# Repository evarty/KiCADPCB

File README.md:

This is the PCB design for various projects. Some have associated uC code, but that is seperate. There are seperate repos for some projects under evarty. A number of these have GCode as well.

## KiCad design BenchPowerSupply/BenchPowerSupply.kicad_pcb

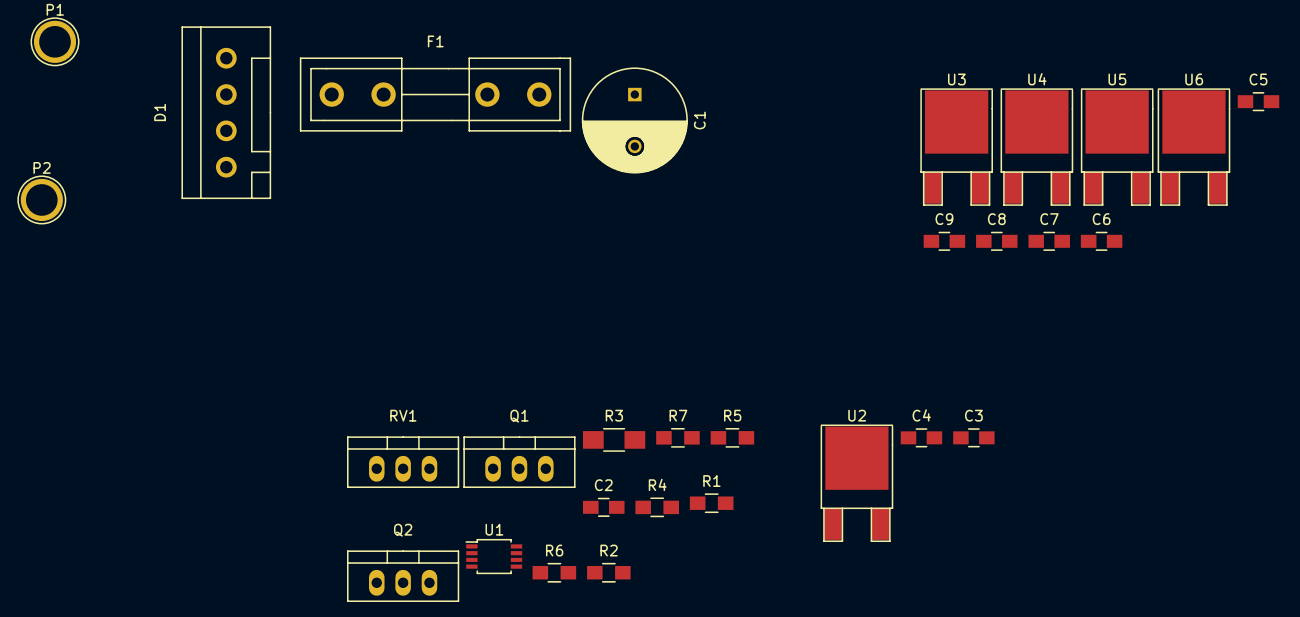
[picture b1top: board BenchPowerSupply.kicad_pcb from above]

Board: 2 copper layers, 29 parts (0 on the bottom side), 17 nets, no tracks yet.

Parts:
C1: 4u7; C_Radial_D10_L13_P5
C2: .1u; C_0805_HandSoldering
C3, C4, C5, C6, C7, C8, C9: C; C_0805_HandSoldering
D1: Diode_Bridge; WAGO_734_4pin_Straight
F1: FUSE; Fuseholder5x20_horiz_open_inline_Type-I
P1, P2: CONN_01X01; 1pin
Q1: Q_NMOS_DGS; TO-220_Neutral123_Vertical
Q2: Q_PMOS_DGS; TO-220_Neutral123_Vertical
R1, R2, R4, R5: 10K; R_0805_HandSoldering
R3: 0R1; R_1206_HandSoldering
R6: 470K; R_0805_HandSoldering
R7: 4K7; R_0805_HandSoldering
RV1: 10K; TO-220_Neutral123_Vertical
U1: TL972; TSSOP-8_3x3mm_Pitch0.65mm
U2, U3: LM7812; TO-252-2Lead
U4: LM7809CT; TO-252-2Lead
U5: LM7805; TO-252-2Lead
U6: LD33V3; TO-252-2Lead

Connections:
15VAC1: D1.4, P1.1
15VAC2: D1.2, P2.1
+12V: C1.2, C2.1, C2.2, C3.2, C4.1, C4.2, C5.2, C6.2, C7.2, C8.2, C9.2, D1.1, Q1.1, R2.2, R7.2, RV1.3, U1.8, U4.2, U6.1
AmplifiedVsense: Q1.3, Q2.2, R6.1, R7.1
unnamed: C6.1, U4.1
unnamed: C7.1, U4.3
unnamed: C8.1, U6.3
unnamed: C9.1, U6.2
unnamed: D1.3, F1.1
unnamed: Q1.2, U1.7
unnamed: R1.2, R2.1, U1.3
unnamed: R4.2, R5.2, U1.2
unnamed: R6.2, RV1.1, RV1.2, U1.6
OutputAfterPassFET: C5.1, Q2.1
OutputAfterRsense: Q2.3, R3.1, R4.1
Rectified: C1.1, C3.1, F1.2, R1.1, R3.2
Vsense: R5.1, U1.1, U1.5

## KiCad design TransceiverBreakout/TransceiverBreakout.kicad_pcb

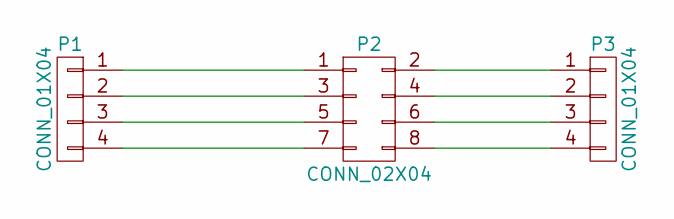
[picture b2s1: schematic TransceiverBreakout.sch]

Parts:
P1, P3: CONN_01X04; Pin_Header_Straight_1x04
P2: CONN_02X04; Pin_Header_Straight_2x04

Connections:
unnamed: P1.1, P2.1
unnamed: P1.2, P2.3
unnamed: P1.3, P2.5
unnamed: P1.4, P2.7
unnamed: P2.2, P3.1
unnamed: P2.4, P3.2
unnamed: P2.6, P3.3
unnamed: P2.8, P3.4

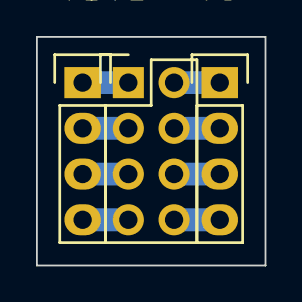
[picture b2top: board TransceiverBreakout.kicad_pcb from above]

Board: 2 copper layers, 12.7 x 12.7 mm, 3 parts (0 on the bottom side), 8 nets.

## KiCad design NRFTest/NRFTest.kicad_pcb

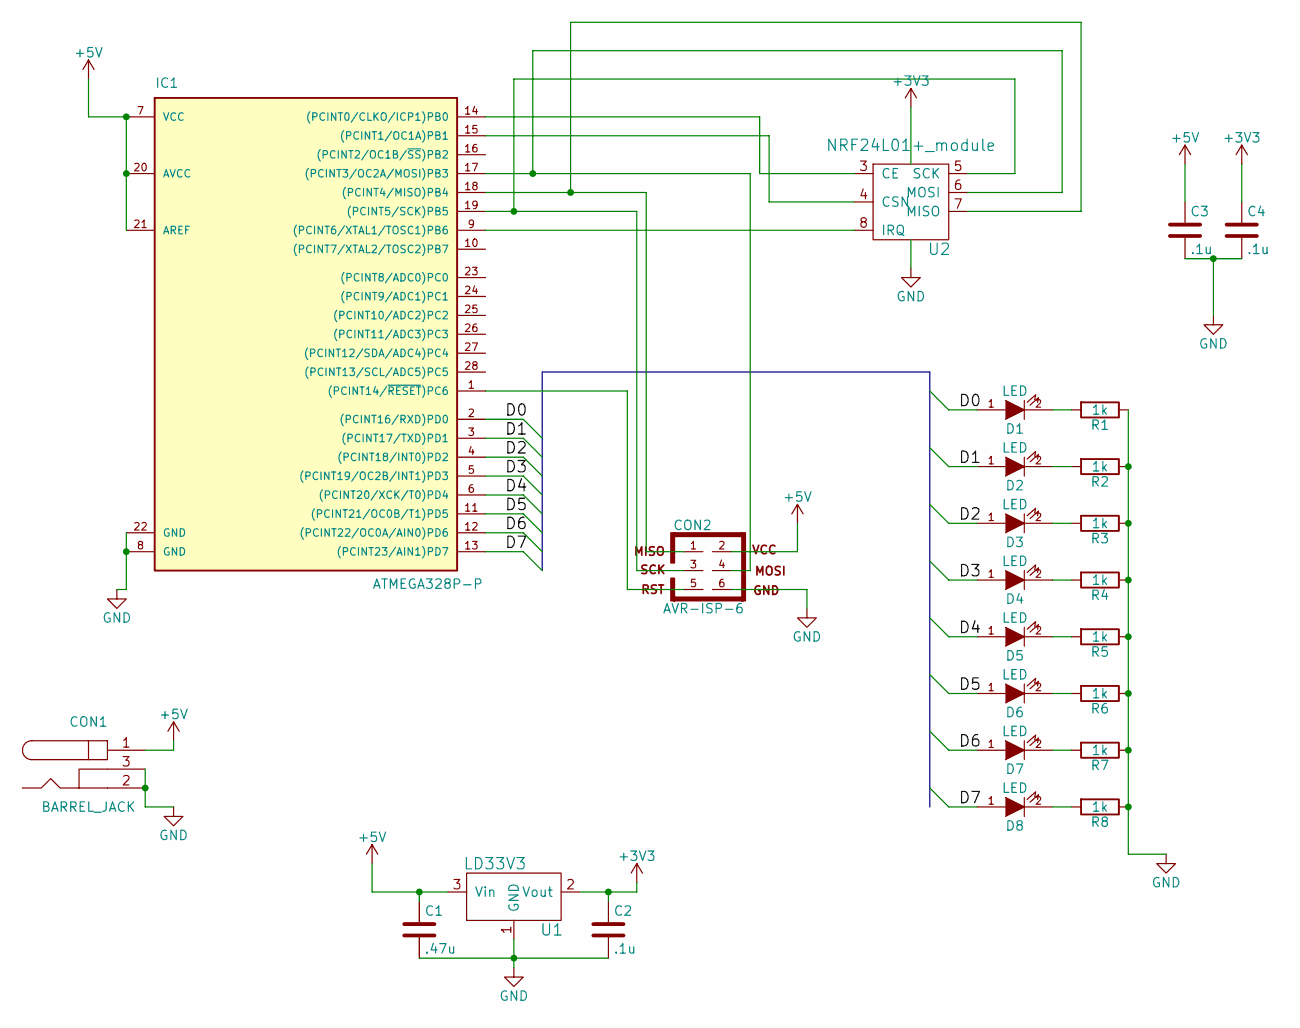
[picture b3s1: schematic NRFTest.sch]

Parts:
C1: .47u; C_Rect_L7_W2.5_P5
C2, C3, C4: .1u; C_Rect_L7_W2.5_P5
CON1: BARREL_JACK
CON2: AVR-ISP-6; Pin_Header_Straight_2x03
D1, D2, D3, D4, D5, D6, D7, D8: LED; LED-5MM
IC1: ATMEGA328P-P; DIP-28_W7.62mm_LongPads
R1, R2, R3, R4, R5, R6, R7, R8: 1k; Resistor_Horizontal_RM15mm
U1: LD33V3; TO-220_Neutral123_Vertical
U2: NRF24L01+_module; Pin_Header_Straight_2x04

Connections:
+3V3: C2.1, C4.1, U1.2 (Vout), U2.1 (GND)
+5V: C1.1, C3.1, CON1.1, CON2.2, IC1.7 (VCC), IC1.20 (AVCC), IC1.21 (AREF), U1.3 (Vin)
/D0: D1.1 (A), IC1.2 ((PCINT16/RXD)PD0)
/D1: D2.1 (A), IC1.3 ((PCINT17/TXD)PD1)
/D2: D3.1 (A), IC1.4 ((PCINT18/INT0)PD2)
/D3: D4.1 (A), IC1.5 ((PCINT19/OC2B/INT1)PD3)
/D4: D5.1 (A), IC1.6 ((PCINT20/XCK/T0)PD4)
/D5: D6.1 (A), IC1.11 ((PCINT21/OC0B/T1)PD5)
/D6: D7.1 (A), IC1.12 ((PCINT22/OC0A/AIN0)PD6)
/D7: D8.1 (A), IC1.13 ((PCINT23/AIN1)PD7)
GND: C1.2, C2.2, C3.2, C4.2, CON1.2, CON1.3, CON2.6, IC1.8 (GND), IC1.22 (GND), R1.1, R2.1, R3.1, R4.1, R5.1, R6.1, R7.1, R8.1, U1.1 (GND), U2.2 (Vcc)
unnamed: CON2.1, IC1.18 ((PCINT4/MISO)PB4), U2.7 (MISO)
unnamed: CON2.3, IC1.19 ((PCINT5/SCK)PB5), U2.5 (SCK)
unnamed: CON2.4, IC1.17 ((PCINT3/OC2A/MOSI)PB3), U2.6 (MOSI)
unnamed: CON2.5, IC1.1 ((PCINT14/~RESET~)PC6)
unnamed: D1.2 (K), R1.2
unnamed: D2.2 (K), R2.2
unnamed: D3.2 (K), R3.2
unnamed: D4.2 (K), R4.2
unnamed: D5.2 (K), R5.2
unnamed: D6.2 (K), R6.2
unnamed: D7.2 (K), R7.2
unnamed: D8.2 (K), R8.2
unnamed: IC1.9 ((PCINT6/XTAL1/TOSC1)PB6), U2.8 (IRQ)
unnamed: IC1.14 ((PCINT0/CLKO/ICP1)PB0), U2.3 (CE)
unnamed: IC1.15 ((PCINT1/OC1A)PB1), U2.4 (CSN)

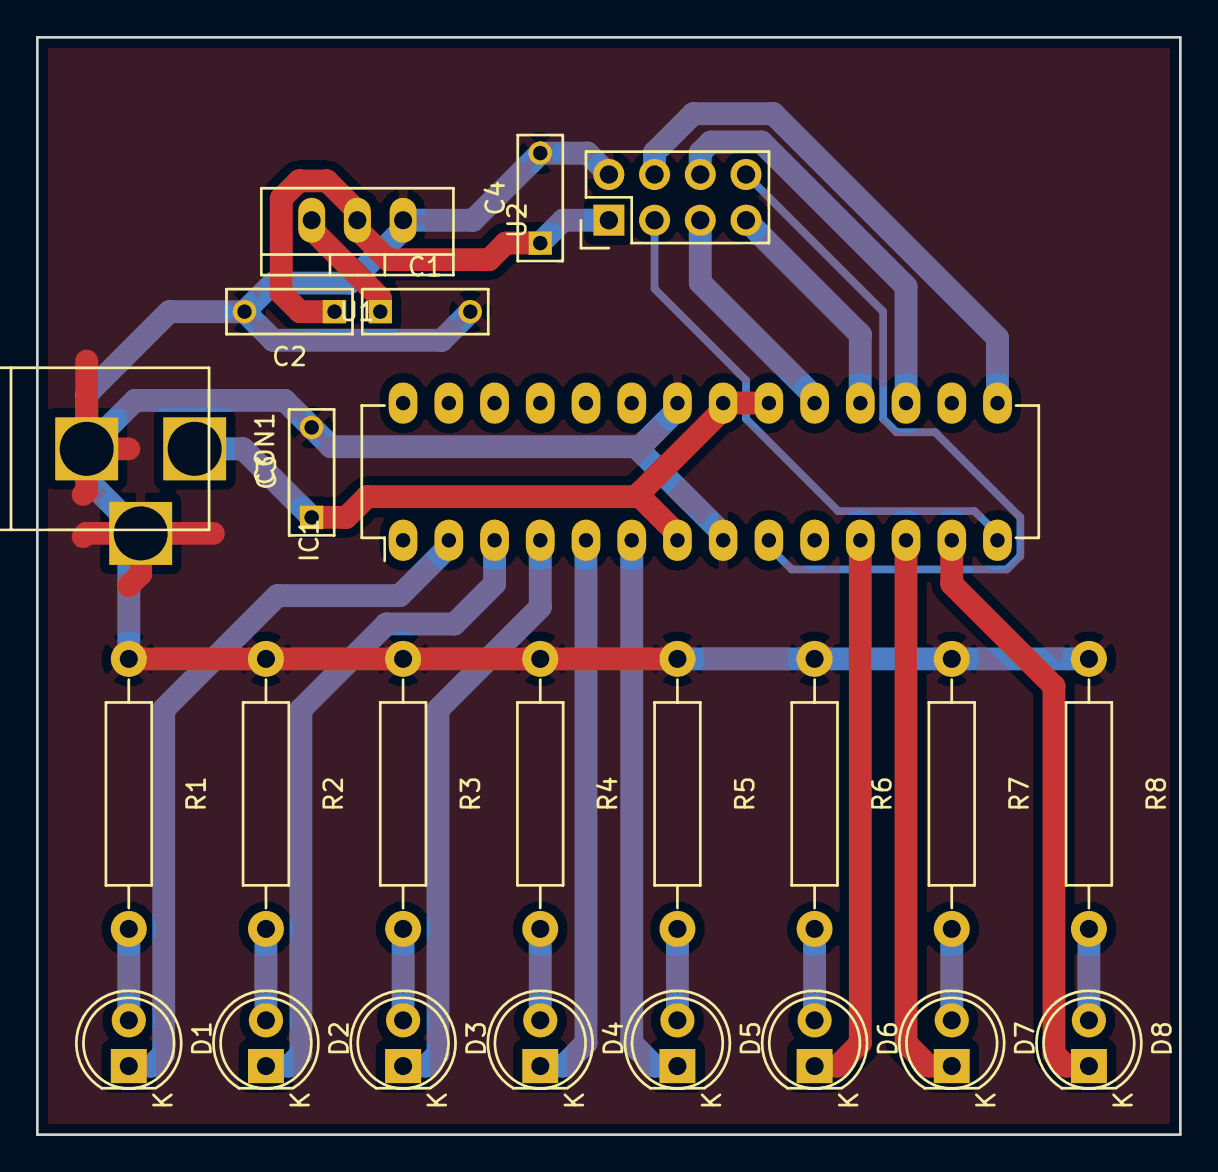
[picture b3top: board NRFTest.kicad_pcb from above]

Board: 2 copper layers, 63.5 x 61.0 mm, 24 parts (0 on the bottom side), 25 nets.

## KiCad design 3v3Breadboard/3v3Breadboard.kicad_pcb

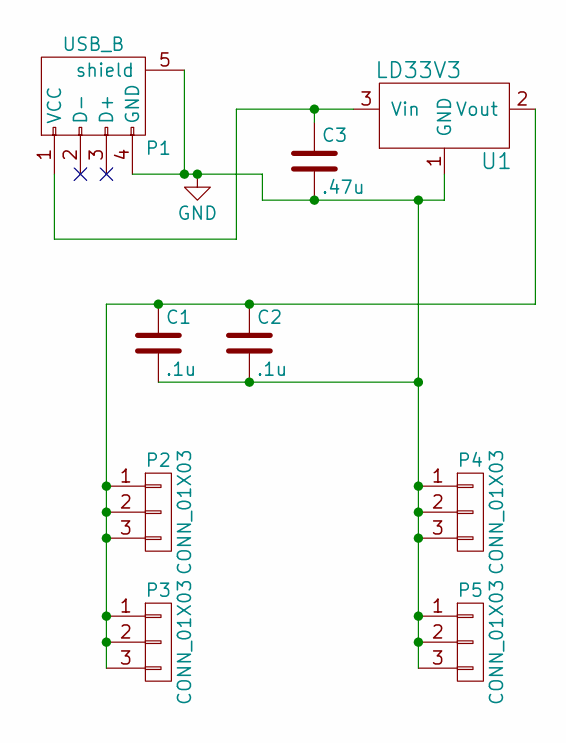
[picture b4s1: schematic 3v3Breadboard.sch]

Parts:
C1, C2: .1u; C_Rect_L7_W2.5_P5
C3: .47u; C_Rect_L7_W2.5_P5
P1: USB_B
P2, P3, P4, P5: CONN_01X03; Pin_Header_Straight_1x03
U1: LD33V3; TO-220_Neutral123_Vertical_LargePads

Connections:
GND: C1.2, C2.2, C3.2, P1.4 (GND), P1.5 (shield), P4.1, P4.2, P4.3, P5.1, P5.2, P5.3, U1.1 (GND)
unnamed: C1.1, C2.1, P2.1, P2.2, P2.3, P3.1, P3.2, P3.3, U1.2 (Vout)
unnamed: C3.1, P1.1 (VCC), U1.3 (Vin)

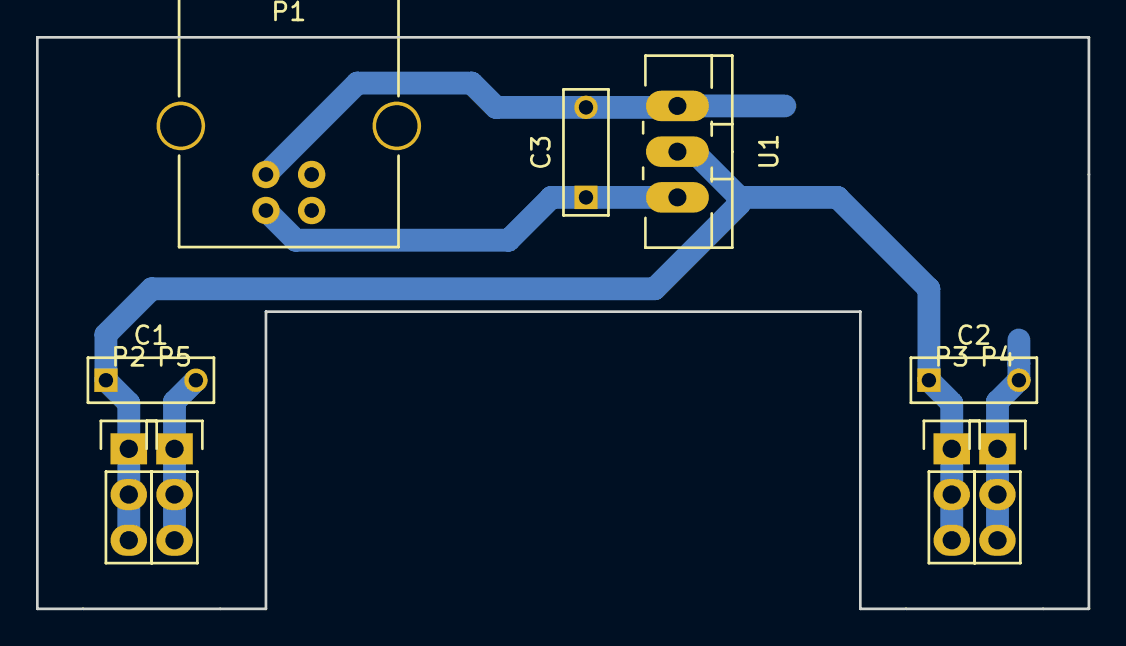
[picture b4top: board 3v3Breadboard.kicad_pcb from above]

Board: 2 copper layers, 58.4 x 31.8 mm, 9 parts (0 on the bottom side), 3 nets.

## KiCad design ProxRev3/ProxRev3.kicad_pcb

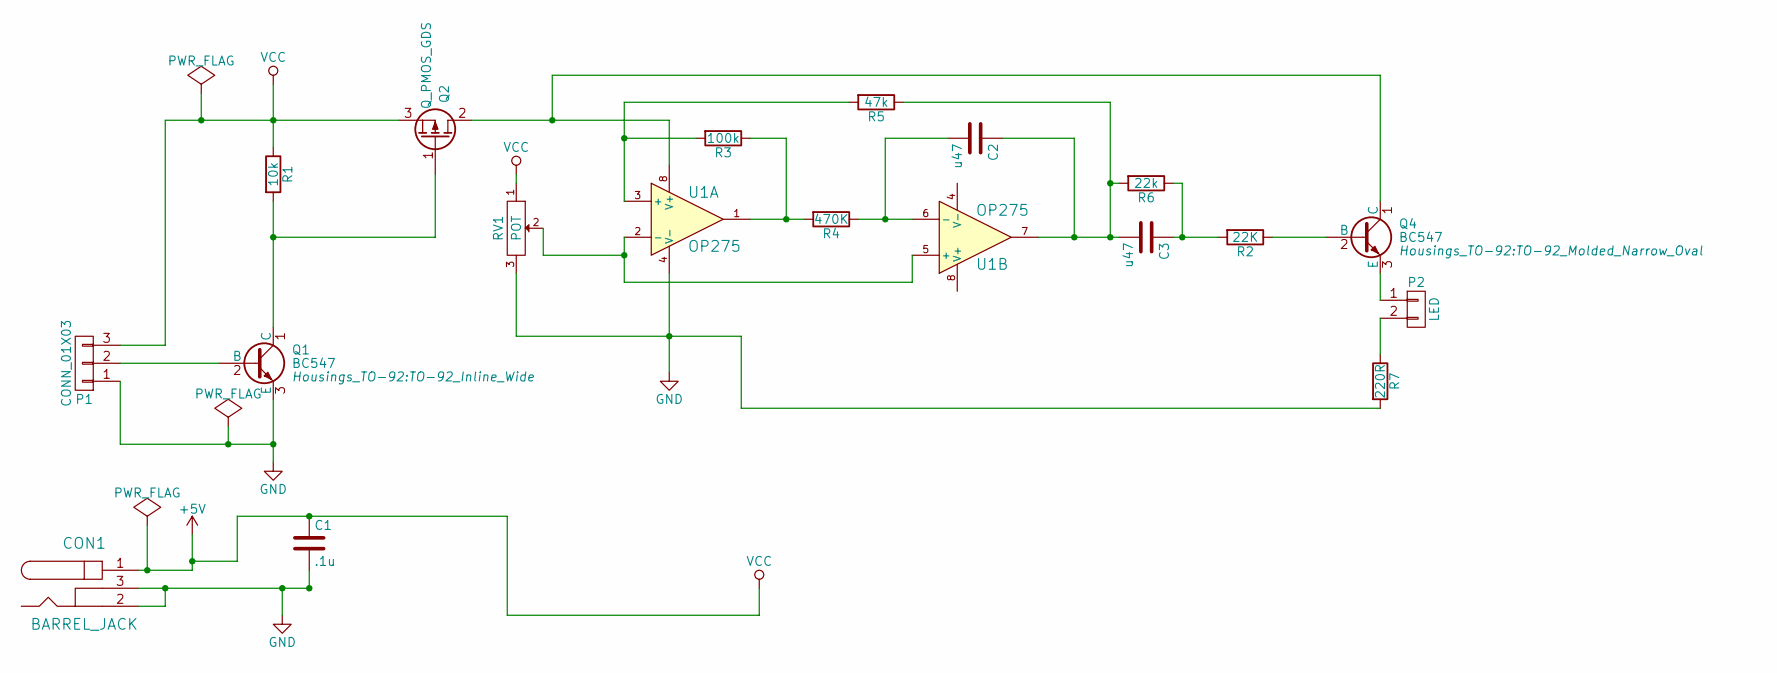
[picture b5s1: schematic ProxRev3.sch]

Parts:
C1: .1u; C_Rect_L7_W2.5_P5
C2, C3: u47; C_Rect_L7_W2.5_P5
CON1: BARREL_JACK
P1: CONN_01X03; Pin_Header_Angled_1x03
P2: LED; Pin_Header_Angled_1x02
Q1: BC547; TO-92_Inline_Wide
Q2: Q_PMOS_GDS; TO-92_Inline_Wide
Q4: BC547; TO-92_Molded_Narrow_Oval
R1: 10k; Resistor_Horizontal_RM10mm
R2: 22K; Resistor_Horizontal_RM10mm
R3: 100k; Resistor_Horizontal_RM10mm
R4: 470K; Resistor_Horizontal_RM10mm
R5: 47k; Resistor_Horizontal_RM10mm
R6: 22k; Resistor_Horizontal_RM10mm
R7: 220R; Resistor_Horizontal_RM10mm
RV1: POT; Potentiometer_Bourns_3339P_Angular_ScrewUp
U1: OP275; DIP-8_W7.62mm_LongPads

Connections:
+5V: C1.1, CON1.1, P1.3, Q2.3 (S), R1.1, RV1.1
GND: C1.2, CON1.2, CON1.3, P1.1, Q1.3 (E), R7.2, RV1.3, U1.4 (V-)
unnamed: C2.1, C3.2, R5.1, R6.2, U1.7
unnamed: C2.2, R4.1, U1.6 (-)
unnamed: C3.1, R2.2, R6.1
unnamed: P1.2, Q1.2 (B)
unnamed: P2.1, Q4.3 (E)
unnamed: P2.2, R7.1
unnamed: Q1.1 (C), Q2.1 (G), R1.2
unnamed: Q2.2 (D), Q4.1 (C), U1.8 (V+)
unnamed: Q4.2 (B), R2.1
unnamed: R3.1, R4.2, U1.1
unnamed: R3.2, R5.2, U1.3 (+)
unnamed: RV1.2, U1.2 (-), U1.5 (+)

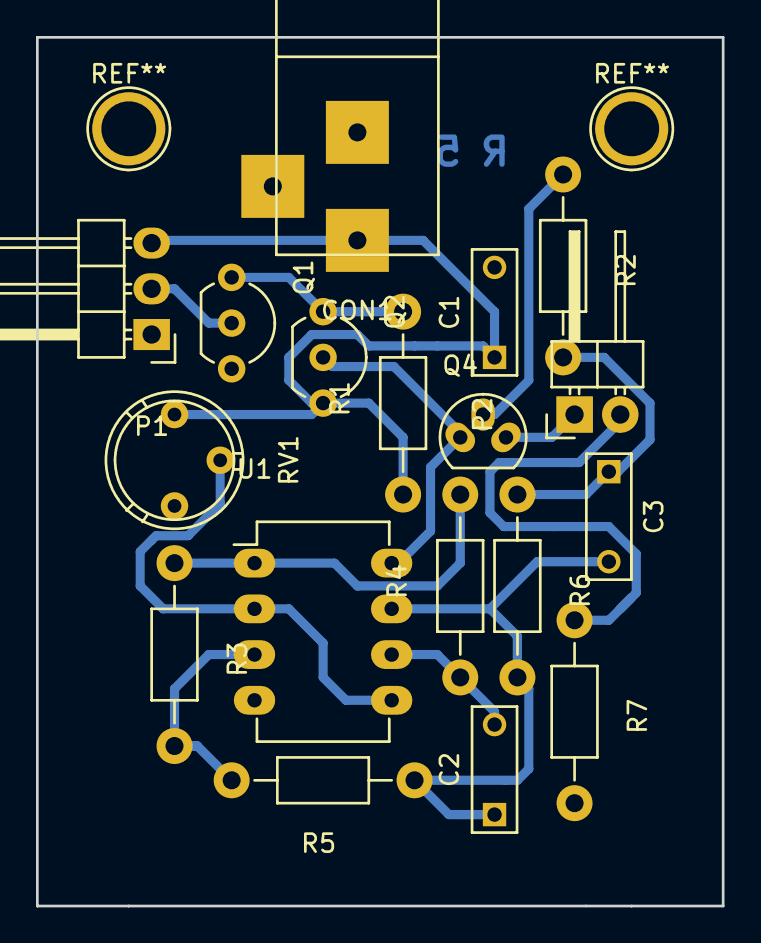
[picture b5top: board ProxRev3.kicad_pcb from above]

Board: 2 copper layers, 38.1 x 48.3 mm, 18 parts (0 on the bottom side), 14 nets.

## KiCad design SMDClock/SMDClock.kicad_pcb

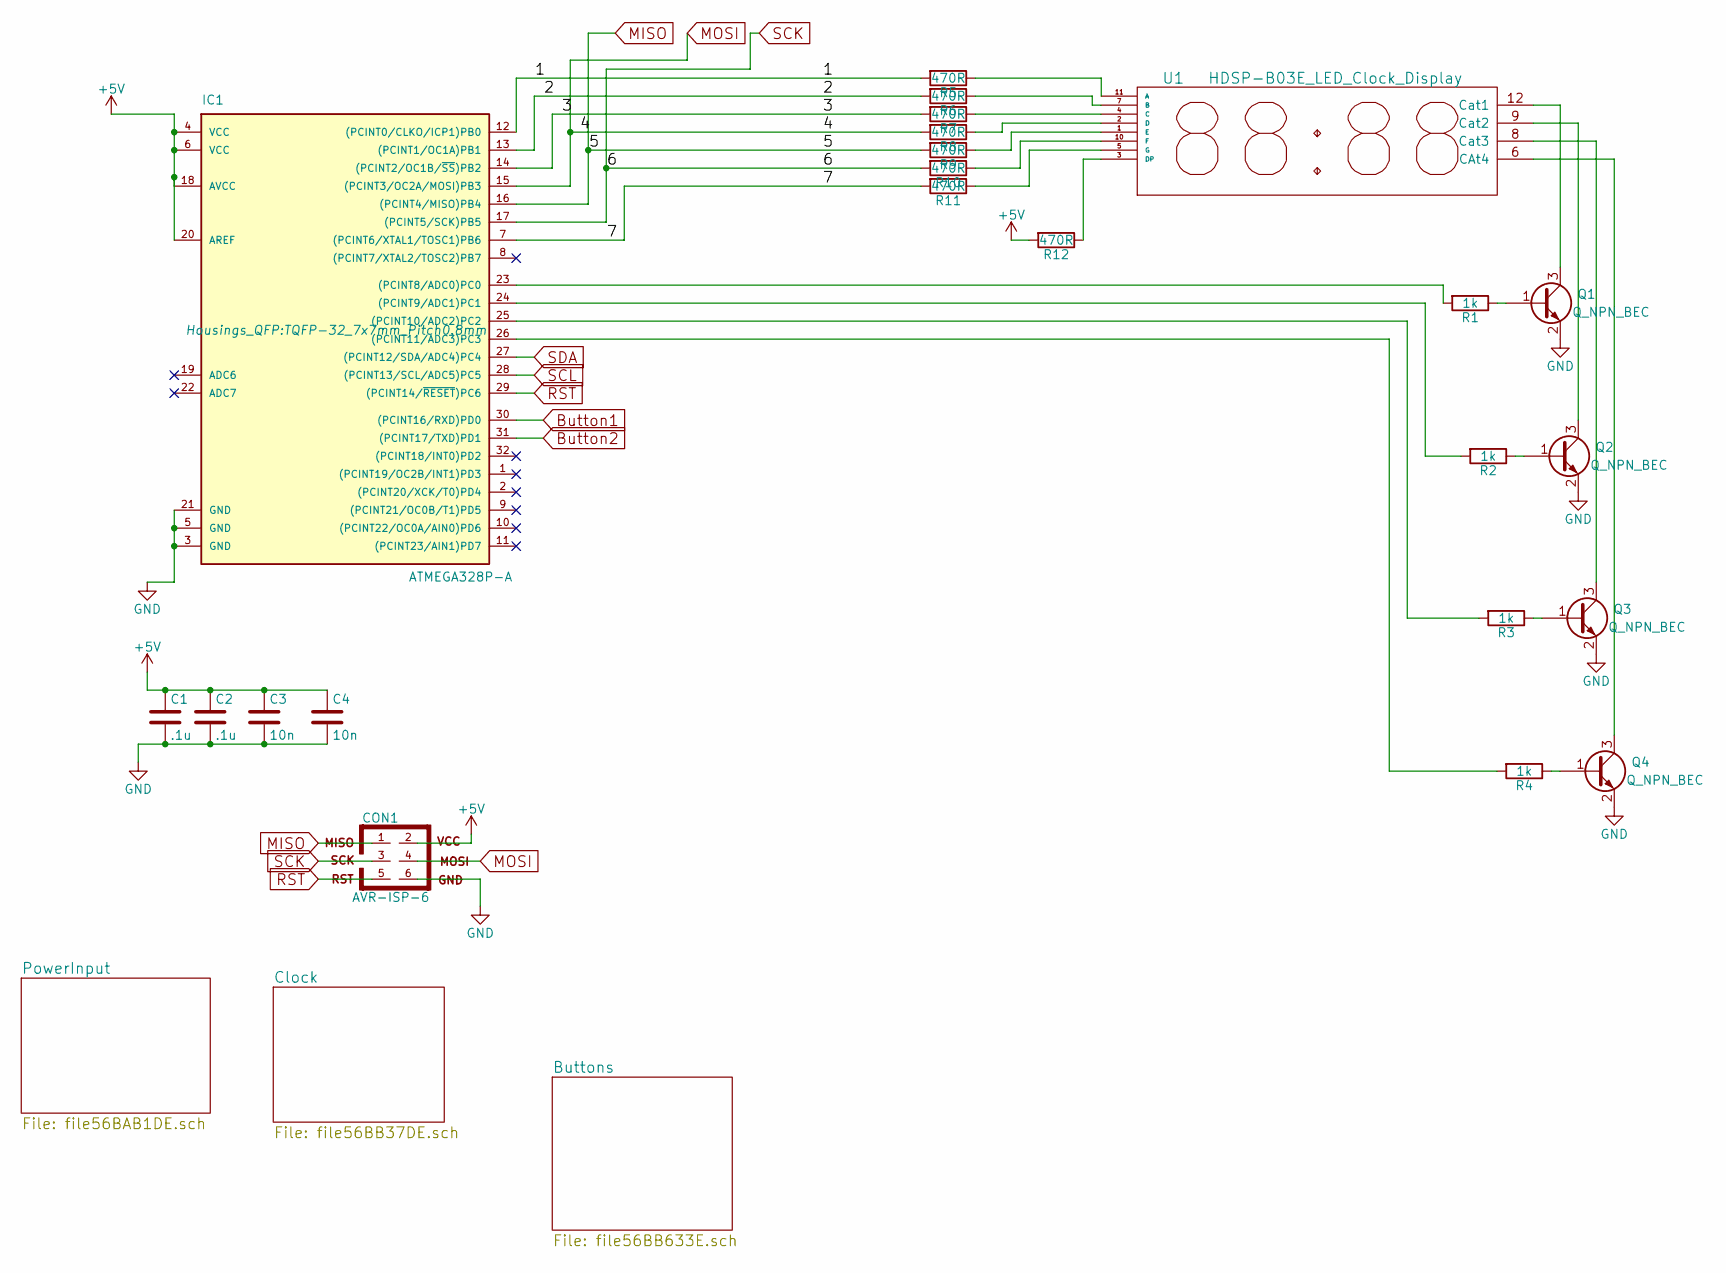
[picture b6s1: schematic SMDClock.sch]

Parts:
C1, C2: .1u; C_0805_HandSoldering
C3, C4: 10n; C_0805_HandSoldering
CON1: AVR-ISP-6; Pin_Header_Straight_2x03
IC1: ATMEGA328P-A; TQFP-32_7x7mm_Pitch0.8mm
Q1, Q2, Q3, Q4: Q_NPN_BEC; SOT-23_Handsoldering
R1, R2, R3, R4: 1k; R_0805_HandSoldering
R5, R6, R7, R8, R9, R10, R11, R12: 470R; R_0805_HandSoldering
U1: HDSP-B03E_LED_Clock_Display; DHDSP-B03E_Footprint

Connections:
+5V: C1.1, C2.1, C3.1, C4.1, CON1.2, IC1.4 (VCC), IC1.6 (VCC), IC1.18 (AVCC), IC1.20 (AREF), R12.2; also elsewhere on the board
/1: IC1.12 ((PCINT0/CLKO/ICP1)PB0), R5.2
/2: IC1.13 ((PCINT1/OC1A)PB1), R6.2
/3: IC1.14 ((PCINT2/OC1B/~SS~)PB2), R7.2
/7: IC1.7 ((PCINT6/XTAL1/TOSC1)PB6), R11.2
Button1: IC1.30 ((PCINT16/RXD)PD0); also elsewhere on the board
Button2: IC1.31 ((PCINT17/TXD)PD1); also elsewhere on the board
GND: C1.2, C2.2, C3.2, C4.2, CON1.6, IC1.3 (GND), IC1.5 (GND), IC1.21 (GND), Q1.2 (E), Q2.2 (E), Q3.2 (E), Q4.2 (E); also elsewhere on the board
MISO: CON1.1, IC1.16 ((PCINT4/MISO)PB4), R9.2
MOSI: CON1.4, IC1.15 ((PCINT3/OC2A/MOSI)PB3), R8.2
unnamed: IC1.23 ((PCINT8/ADC0)PC0), R1.2
unnamed: IC1.24 ((PCINT9/ADC1)PC1), R2.2
unnamed: IC1.25 ((PCINT10/ADC2)PC2), R3.2
unnamed: IC1.26 ((PCINT11/ADC3)PC3), R4.2
unnamed: Q1.1 (B), R1.1
unnamed: Q1.3 (C), U1.12 (Cat1)
unnamed: Q2.1 (B), R2.1
unnamed: Q2.3 (C), U1.9 (Cat2)
unnamed: Q3.1 (B), R3.1
unnamed: Q3.3 (C), U1.8 (Cat3)
unnamed: Q4.1 (B), R4.1
unnamed: Q4.3 (C), U1.6 (CAt4)
unnamed: R5.1, U1.11 (A)
unnamed: R6.1, U1.7 (B)
unnamed: R7.1, U1.4 (C)
unnamed: R8.1, U1.2 (D)
unnamed: R9.1, U1.1 (E)
unnamed: R10.1, U1.10 (F)
unnamed: R11.1, U1.5 (G)
unnamed: R12.1, U1.3 (DP)
RST: CON1.5, IC1.29 ((PCINT14/~RESET~)PC6)
SCK: CON1.3, IC1.17 ((PCINT5/SCK)PB5), R10.2
SCL: IC1.28 ((PCINT13/SCL/ADC5)PC5); also elsewhere on the board
SDA: IC1.27 ((PCINT12/SDA/ADC4)PC4); also elsewhere on the board

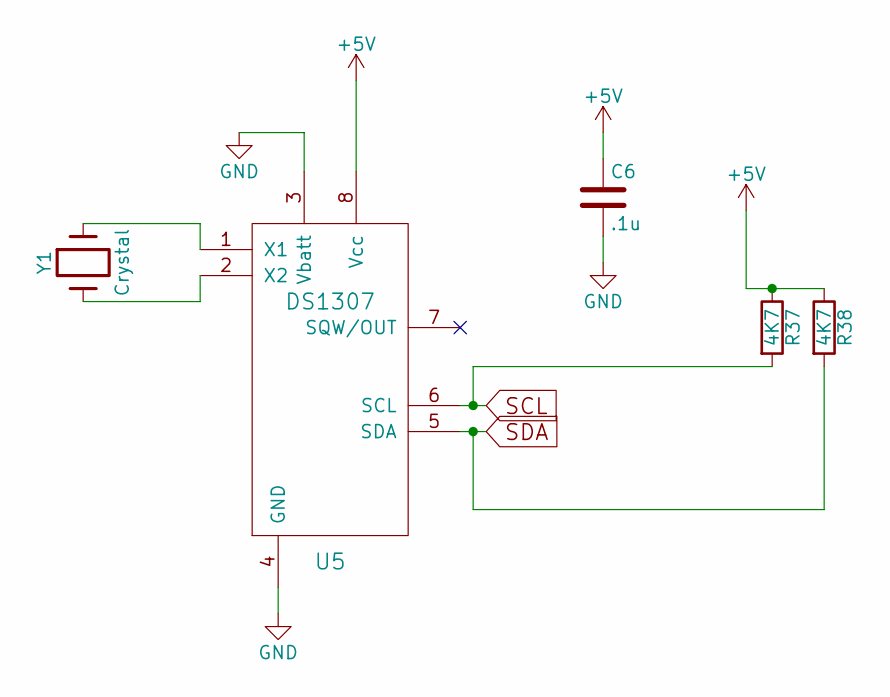
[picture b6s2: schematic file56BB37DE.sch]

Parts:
C6: .1u; C_0805_HandSoldering
R37, R38: 4K7; R_0805_HandSoldering
U5: DS1307; SOIC-8_3.9x4.9mm_Pitch1.27mm
Y1: Crystal; Crystal_Watch

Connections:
+5V: C6.1, R37.1, R38.1, U5.8 (Vcc); also elsewhere on the board
GND: C6.2, U5.3 (Vbatt), U5.4 (GND); also elsewhere on the board
unnamed: U5.1 (X1), Y1.1
unnamed: U5.2 (X2), Y1.2
SCL: R37.2, U5.6 (SCL); also elsewhere on the board
SDA: R38.2, U5.5 (SDA); also elsewhere on the board

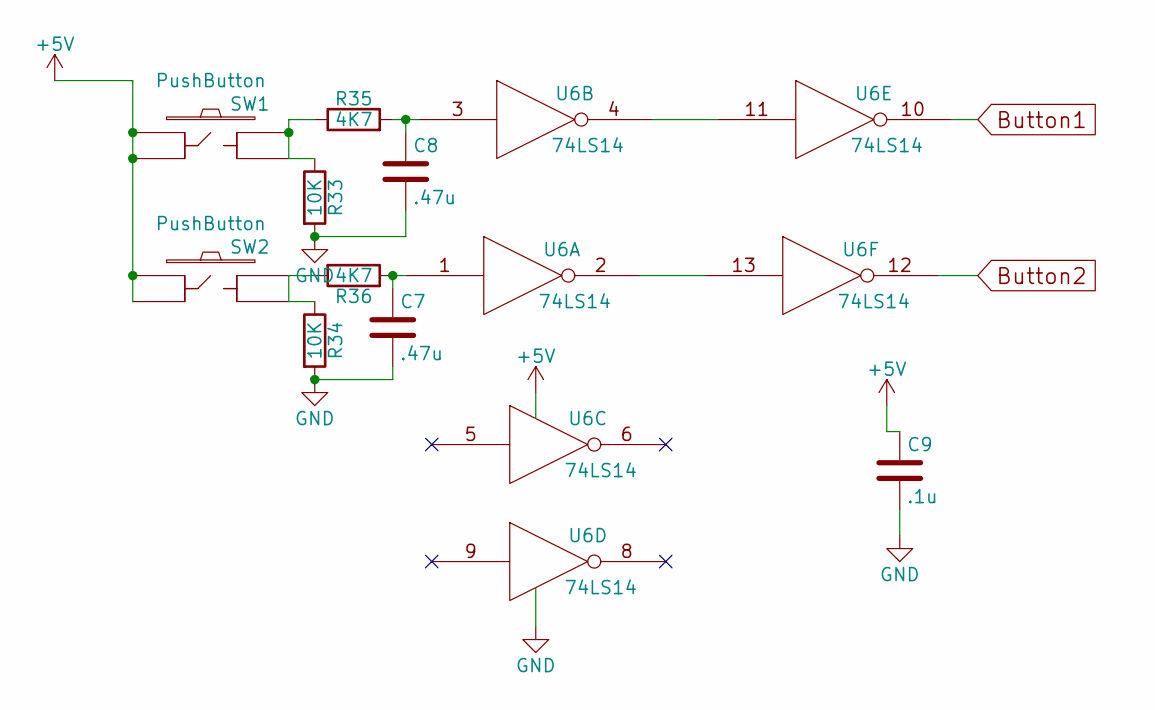
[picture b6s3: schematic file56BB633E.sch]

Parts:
C7, C8: .47u; C_0805_HandSoldering
C9: .1u; C_0805_HandSoldering
R33, R34: 10K; R_0805_HandSoldering
R35, R36: 4K7; R_0805_HandSoldering
SW1, SW2: PushButton
U6: 74LS14; SOIC-14_N

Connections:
+5V: C9.1, SW1.1, SW1.4, SW2.1, SW2.4, U6.14 (VCC); also elsewhere on the board
Button1: U6.10; also elsewhere on the board
Button2: U6.12; also elsewhere on the board
GND: C7.2, C8.2, C9.2, R33.2, R34.2, U6.7 (GND); also elsewhere on the board
unnamed: C7.1, R36.1, U6.1
unnamed: C8.1, R35.2, U6.3
unnamed: R33.1, R35.1, SW1.2, SW1.3
unnamed: R34.1, R36.2, SW2.2, SW2.3
unnamed: U6.4, U6.11
unnamed: U6.2, U6.13

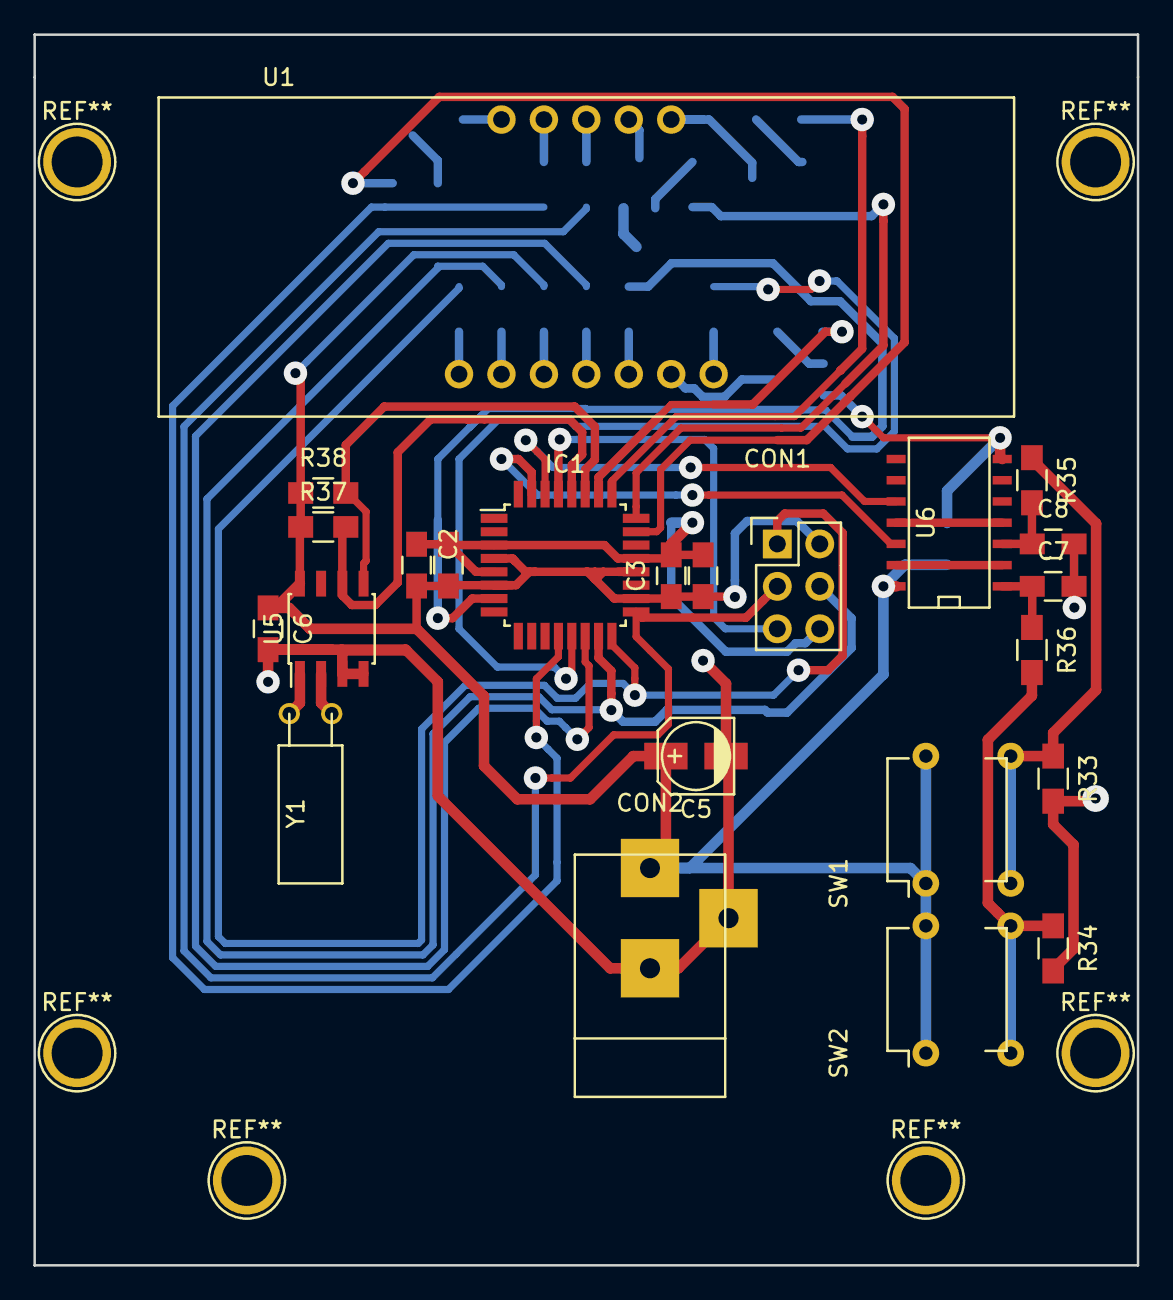
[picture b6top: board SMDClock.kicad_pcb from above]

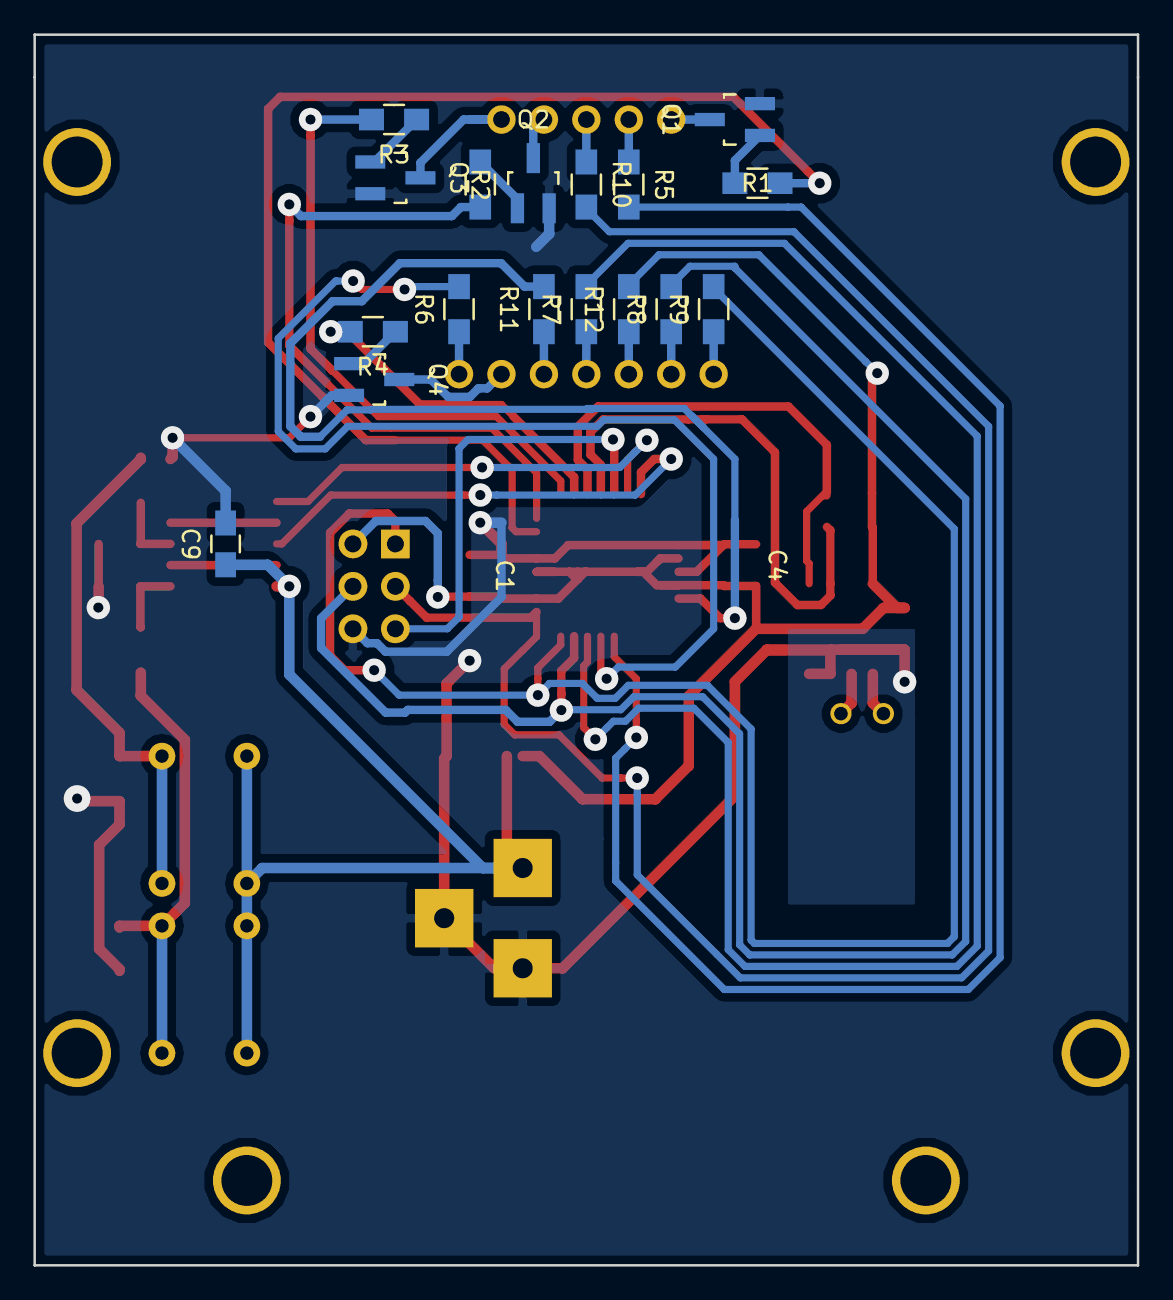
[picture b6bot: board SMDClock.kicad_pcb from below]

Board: 2 copper layers, 66.0 x 73.7 mm, 40 parts (17 on the bottom side), 42 nets.

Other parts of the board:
C5: 100u; c_elec_4x4.5
CON2: BARREL_JACK

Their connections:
+5V: C5.1, CON2.1; also elsewhere on the board
GND: C5.2, CON2.2, CON2.3; also elsewhere on the board

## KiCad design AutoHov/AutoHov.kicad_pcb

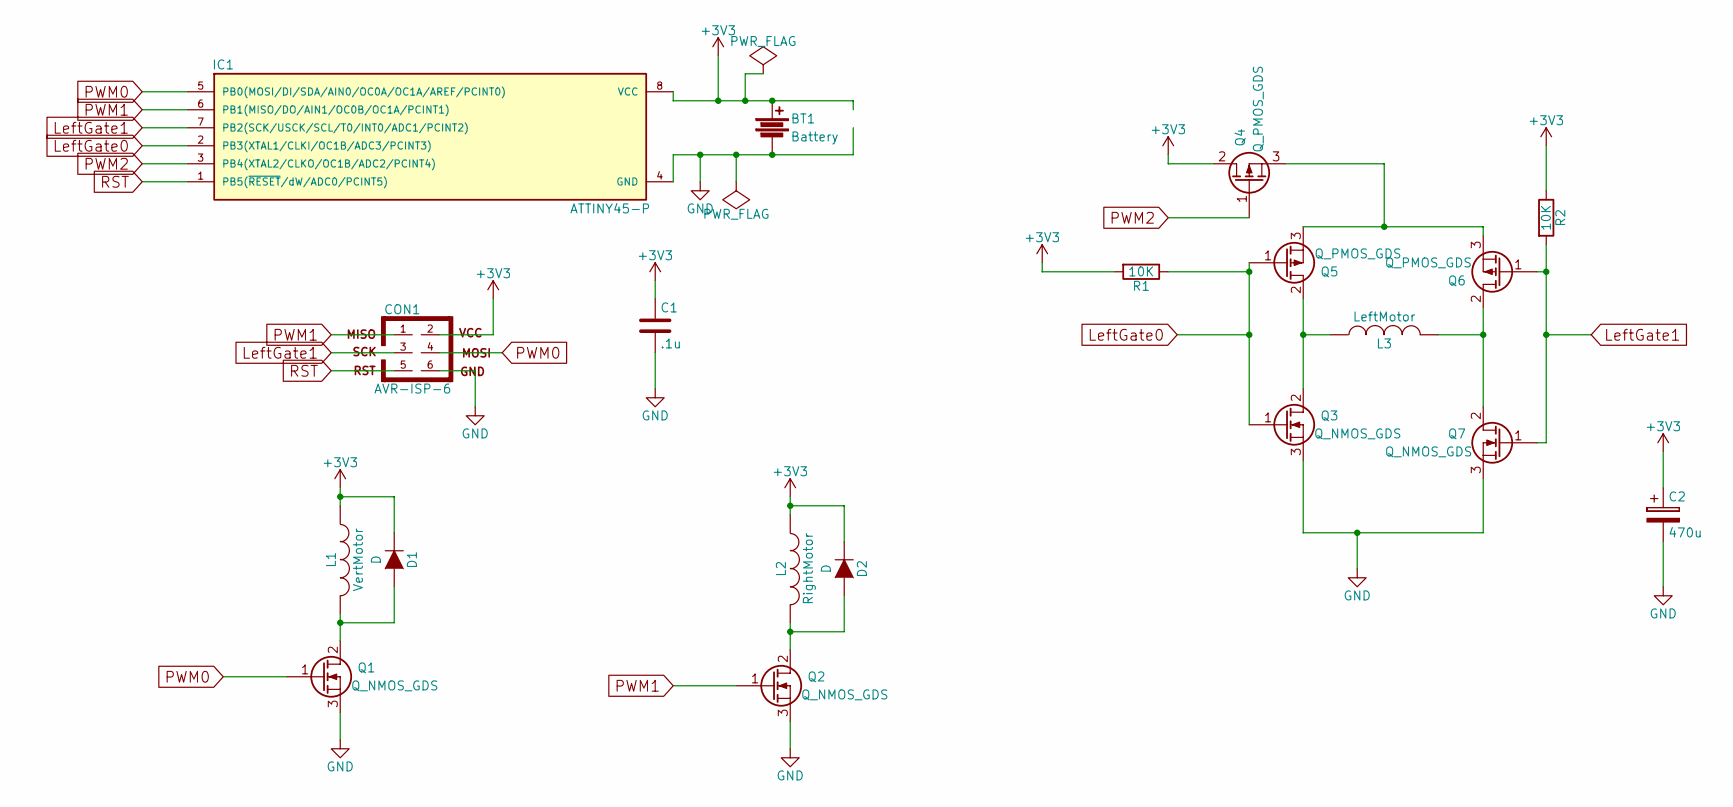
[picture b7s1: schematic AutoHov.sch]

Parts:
BT1: Battery; Pin_Header_Straight_1x02
C1: .1u; C_Rect_L7_W2.5_P5
C2: 470u; C_Radial_D10_L13_P5
CON1: AVR-ISP-6; Pin_Header_Straight_2x03
D1, D2: D; Diode_DO-35_SOD27_Horizontal_RM10
IC1: ATTINY45-P; DIP-8_W7.62mm_LongPads
L1: VertMotor; Pin_Header_Straight_1x02
L2: RightMotor; Pin_Header_Straight_1x02
L3: LeftMotor; Pin_Header_Straight_1x02
Q1, Q2, Q3, Q7: Q_NMOS_GDS; Pin_Header_Straight_1x03
Q4, Q5, Q6: Q_PMOS_GDS; Pin_Header_Straight_1x03
R1, R2: 10K; Resistor_Vertical_RM5mm

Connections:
+3V3: BT1.1, C1.1, C2.1, CON1.2, D1.1 (K), D2.1 (K), IC1.8 (VCC), L1.1, L2.1, Q4.2 (D), R1.2, R2.1
GND: BT1.2, C1.2, C2.2, CON1.6, IC1.4 (GND), Q1.3 (S), Q2.3 (S), Q3.3 (S), Q7.3 (S)
LeftGate0: IC1.2 (PB3(XTAL1/CLKI/OC1B/ADC3/PCINT3)), Q3.1 (G), Q5.1 (G), R1.1
LeftGate1: CON1.3, IC1.7 (PB2(SCK/USCK/SCL/T0/INT0/ADC1/PCINT2)), Q6.1 (G), Q7.1 (G), R2.2
unnamed: D1.2 (A), L1.2, Q1.2 (D)
unnamed: D2.2 (A), L2.2, Q2.2 (D)
unnamed: L3.1, Q3.2 (D), Q5.2 (D)
unnamed: L3.2, Q6.2 (D), Q7.2 (D)
unnamed: Q4.3 (S), Q5.3 (S), Q6.3 (S)
PWM0: CON1.4, IC1.5 (PB0(MOSI/DI/SDA/AIN0/OC0A/OC1A/AREF/PCI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), Q1.1 (G)
PWM1: CON1.1, IC1.6 (PB1(MISO/DO/AIN1/OC0B/OC1A/PCINT1)), Q2.1 (G)
PWM2: IC1.3 (PB4(XTAL2/CLKO/OC1B/ADC2/PCINT4)), Q4.1 (G)
RST: CON1.5, IC1.1 (PB5(~RESET~/dW/ADC0/PCINT5))

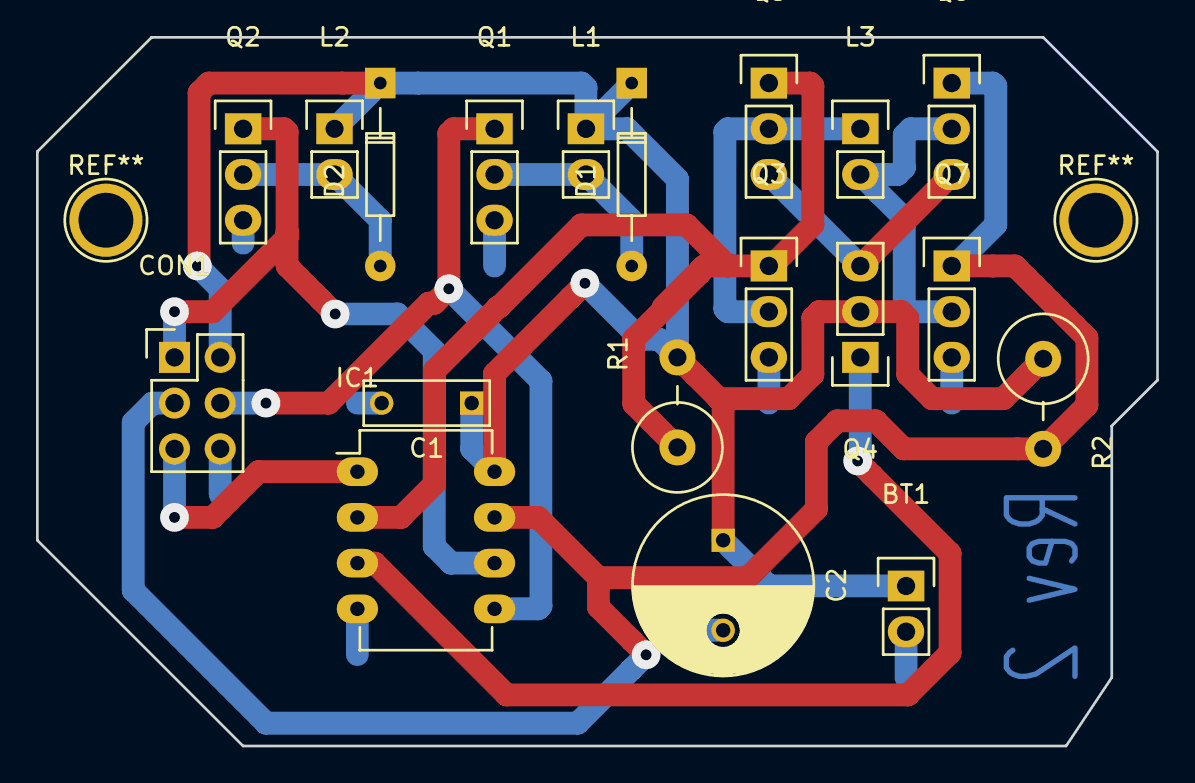
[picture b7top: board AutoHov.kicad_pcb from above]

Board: 2 copper layers, 62.2 x 39.4 mm, 19 parts (0 on the bottom side), 13 nets.

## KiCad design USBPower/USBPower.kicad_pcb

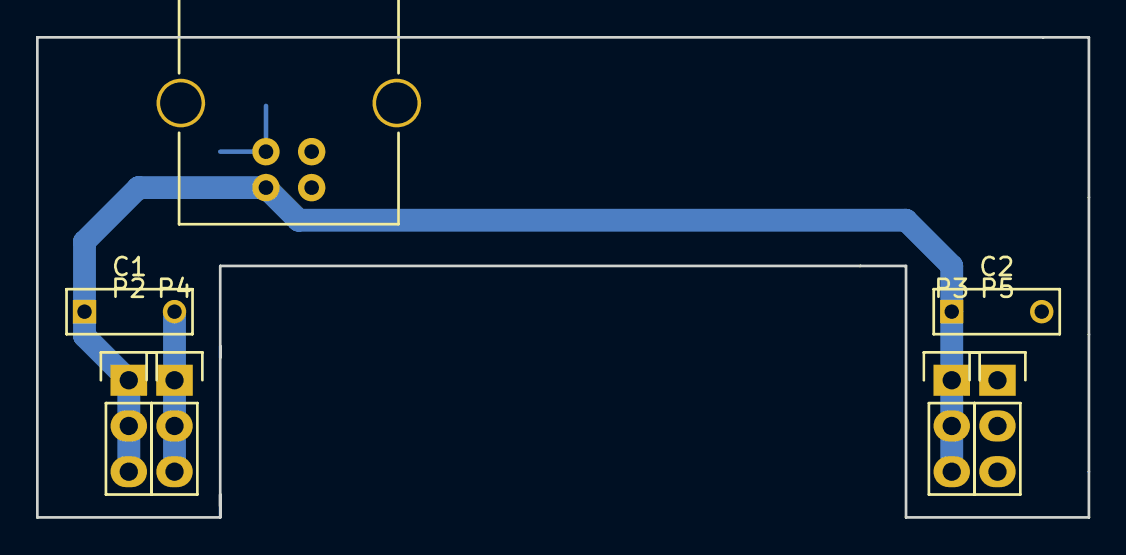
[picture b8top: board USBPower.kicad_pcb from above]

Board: 2 copper layers, 58.4 x 26.7 mm, 7 parts (0 on the bottom side), 2 nets.

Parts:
C1, C2: .47u; C_Rect_L7_W2.5_P5
P1: USB_B
P2, P3, P4, P5: CONN_01X03; Pin_Header_Straight_1x03

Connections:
+5V: C1.1, C2.1, P1.1, P2.1, P2.2, P2.3, P3.1, P3.2, P3.3
GND: C1.2, C2.2, P1.4, P1.5, P4.1, P4.2, P4.3, P5.1, P5.2, P5.3
